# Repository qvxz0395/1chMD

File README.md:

# MD
## 要求仕様
  - 1ch
  - RZ735VA500W駆動可能
  - 出来ればPWM周波数50kHz(maxon motor controllerと同じ値)
  - 正転逆転
  - 電流制御
  - 速度制御
  - AMT102対応
  - CAN通信
  - 超小型,ターミナル方式

## 部品
  - メインマイコン
    - [STM32F042K6T6](http://akizukidenshi.com/catalog/g/gI-10789/)
    - [データシート](https://www.st.com/resource/en/datasheet/stm32f042c4.pdf) 
    - [リファレンスマニュアル](https://www.aps-web.jp/magazine/st/data/STM32F0x1_2_8RM_RM0091_JPN_rev1.pdf)

      - 250YEN
      - CAN 
      - 電流検出ADC12Bit
      - 書き込みデバッグ JTAG
      - ロータリーエンコーダ入力
      - とりあえず生やしとくピン
        - 4PDIPスイッチ
        - SPI1ch
        - USART1ch

  - CANトランシーバ
    - [ATA6561-GAQW-N](https://www.digikey.jp/product-detail/ja/microchip-technology/ATA6561-GAQW-N/ATA6561-GAQW-NCT-ND/9453180)
      - 63YEN
      - SOIC08
      - 電源 5V
      - 

  - 電流センサ
    - [ACS781KLRTR-150U-T](https://www.digikey.jp/product-detail/ja/allegro-microsystems-llc/ACS781KLRTR-150U-T/620-1851-1-ND/6677748)
      - 605YEN
      - ホール効果での電流検出
      - 検出可能電流 0~100[A] 過渡的に150[A], 17.6mV/A
      - 絶対最大定格 285[A],25℃
      - 

  - FET
    - [FDBL86561-F085](https://www.digikey.jp/product-detail/ja/on-semiconductor/FDBL86561-F085/FDBL86561-F085CT-ND/5209201)
      - 450 YEN @1
      - ドレインソース間電圧$V_{dss}$= 60[V]
      - ドレインソース間連続電流( $V_{gs}$ = 10[V], $T_c$ = 25[℃]) $I_D$= 300[A]
      - $I_d,V_{gs}$印加時の$R_{ds} On$= 1.1[mΩ] (max) @ 80[A] , 10[V]
      - $V_{gs}$印加時のゲート電荷 $Q_g$= 220[nC] (max) @10[V]
      - パッケージ　8-PowerSFN
    - 似た特性,同じパッケージのFET
      - [IPT007N06NATMA1](https://www.digikey.jp/product-detail/ja/infineon-technologies/IPT007N06NATMA1/IPT007N06NATMA1CT-ND/4571878)
      - [FDBL0110N60](https://www.digikey.jp/product-detail/ja/on-semiconductor/FDBL0110N60/FDBL0110N60CT-ND/5216101)

  - ゲートドライバ
    - [A3921KLPTR-T](http://akizukidenshi.com/catalog/g/gI-12293/)
      - 350YEN
      - フルブリッジMOSFETドライバ

  - 3.3Vレギュレータ
    - [NJM2845DL1-33](http://akizukidenshi.com/catalog/g/gI-11299/)
      - 50YEN
      - 最大入力電圧 14[V]
      - 出力電流　0.8[A]

  - 5Vレギュレータ
    - [NJM7805SDL1](http://akizukidenshi.com/catalog/g/gI-11237/)
      - 30YEN
      - 最大入力電圧 35[V]
      - 出力電流 1.5[A]

  - デジタルアイソレータ
    - [ADuM7440](https://www.digikey.jp/product-detail/ja/analog-devices-inc/ADUM7440ARQZ-RL7/ADUM7440ARQZ-RL7CT-ND/3897187)
      - 605YEN
      - 電源電圧 3-5.5[V]
      - 4Ch
      - データレート 1[Mbps]

  - モード変更用DIPSW
    - [EHS104LD](http://akizukidenshi.com/catalog/g/gP-05064/)

  - ショットキーバリアダイオード
    - 
## 計算(パワー回路設計)
  - [TeXコマンドをmarkdownでつかう方法](https://qiita.com/kgoto/items/2452b6dbaed5b3f7df78)

### ゲート抵抗
  - [参考](https://detail-infomation.com/gate-driver-gate-resistance-design/)

  FDBL86561-F085 のデータシートの表 Electrical Characteristics より
  
  Total Gate Charge $Q_g$ = 170[nC] (typ.) @ 10V 

  これより，

  ゲート駆動電圧 = 10[V]

  A3921KLPTR-T のデータシート表 ELECTRICAL CHARACTERISTICS Pulldown On Resistance 内の $I_{GHx} , I_{GLx}$より
  
  ゲート電流$I_G$= 150[mA]
  
  ゲート駆動回路の出力電圧$V_{OUT}= V_{REG} = 12.8[V]$より，(A3921の電気特性表より)

  ゲート抵抗$R_G$は

  $$ R_G = \dfrac{V_{out}}{I_G} = \dfrac{12.8[V]}{0.15[A]} = 85[Ω] $$

  ところで，
  電流iを時間tで積分したものが電荷$Q$なので，

  $$Q = \int idt$$

  ゲート電流$i_G$が時間$t_{ON}$流れることで，ゲートに蓄えられた電荷量が$Q_g$になる．

  $$Q_g = \int_0^{t_{ON}} I_G dt = I_G [t]_0^{t_{ON}} = I_G t_{ON}$$

  上記の関係より，

  $$ t_{ON} = \dfrac{Q_g}{t_{ON}} = \dfrac{170[nC]}{0.15[A]} = 1134[ns] $$

### デッドタイム

### チャージポンプコンデンサ

### ブートストラップコンデンサ

### 正逆転確認LEDの電流制限抵抗

### FFの電流制限抵抗

### 5V電源の電流制限抵抗

### 周波数

### 発熱

FETの発熱を考える．([参考](https://lab.fujiele.co.jp/articles/3129/))
他で発熱を考える必要があるのはゲートドライバICだけど，今回は無視．

損失は主に2種類ある．「オン抵抗と電流」によるものと「スイッチング損失」によるもの．

#### オン抵抗と電流

  $P = I^2R$

#### スイッチング損失

  FETはスイッチング時に損失が発生する．損失の式は．

  $ああああああ$

## マイコン関連

### ロータリーエンコーダ
  - [参考(STM32＋HALでエンコーダ―モード)](https://garberas.com/archives/244)

  - [参考(3.3V-5Vレベル変換)](http://kosakai.world.coocan.jp/change_3_3V_5V.html)

#### 回路
  よく使うインクリメンタルエンコーダ[AMT102](https://www.cui.com/product/resource/amt10.pdf)は電源$VDD=5$[V]駆動で,
  パルス信号出力も5[V]である．
  
  しかし，マイコンは3.3V駆動である．

  そのため，マイコンのピンの耐圧が5V以下だった場合，出力信号を[分圧](http://www.kairo-nyumon.com/resistor_divider.html)して電圧を落とさないといけない．

  マイコンの耐圧を確認する．今回の設計ではPA6とPB5,PB6が，エンコーダに接続されている．  
  データシートのP33からあるTable.13 pin definitionによると，それぞれのピンのI/O structureは順にTTa,FT,FTfである．  
  Table.12によると，TTaの耐圧が3.3V, FT,FTfの耐圧が5Vとなっている．また，Table18の絶対最大定格にはFT,FTfも内部プルアップ，プルダウンをすると**耐圧が下がる**と注3に書いてあるので，気を付ける．
  
  PA6だけは分圧必須である．（もう発注しちゃった，，，2019/08/21回路図及び配線図を修正）

#### プログラム

リファレンスマニュアルp341～にエンコーダインターフェースモードについての説明がある．

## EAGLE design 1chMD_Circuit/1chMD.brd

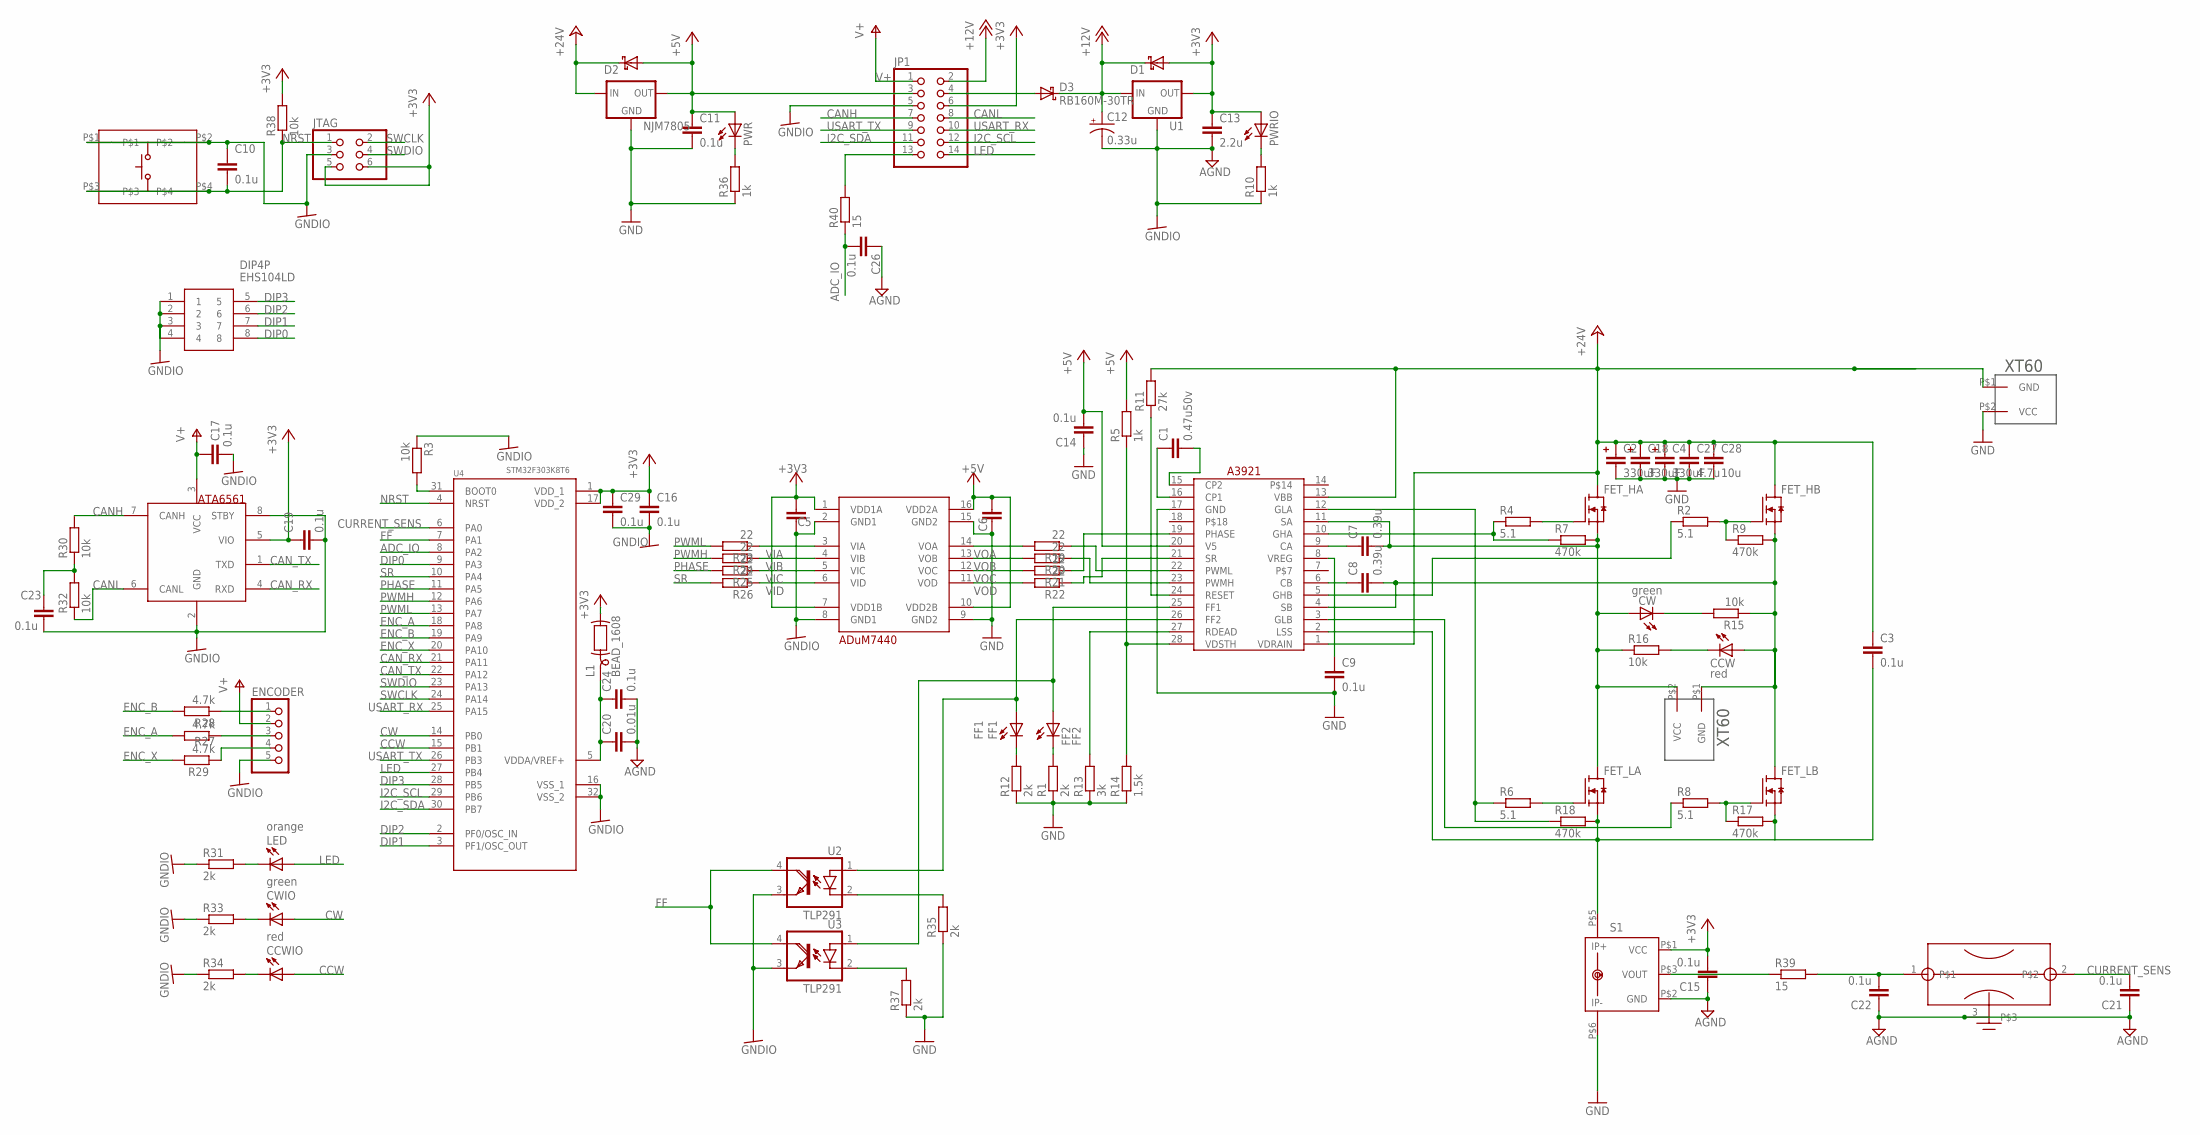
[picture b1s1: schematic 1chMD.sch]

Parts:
A3921: A3921; TSSOP28
ADUM7440: ADUM7440; QSOP16
ATA6561: ATA6561; SO_8
C1: 0.47u50v; 1608
C2, C4, C18: 330uF; PANASONIC_G
C3, C9, C10, C11, C14, C15, C16, C17, C19, C21, C22, C23, C24, C26, C29: 0.1u; 1608
C5, C6: C_1608; 1608
C7, C8: 0.39u; 1608
C12: 0.33u; PANASONIC_C
C13: 2.2u; 1608
C20: 0.01u; 1608
C25: NFM18PS474R0J3D; 1608_EMIFIL
C27: 4.7u; C0805K
C28: 10u; C1210K
CCW: red; 1608_POLE
CCWIO: red; 1608_POLE
CW: green; 1608_POLE
CWIO: green; 1608_POLE
D1, D2: RB751S-40; 1608_POLE
D3: RB160M-30TR; SODFL260X160X90L70X90N
DIP4P: EHS104LD
ENCODER: PINHD-1X5/90; 1X05/90
FET_HA: FDBL86561_F085; PG-HSOF-8-1
FET_HB: FDBL86561_F085; PG-HSOF-8-1
FET_LA: FDBL86561_F085; PG-HSOF-8-1
FET_LB: FDBL86561_F085; PG-HSOF-8-1
FF1: FF1; 1608_POLE
FF2: FF2; 1608_POLE
JP1: PINHD-2X7/90; 2X07/90
JTAG: PINHD-2X3/90; 2X03/90
L1: BEAD_1608; 1608
LED: orange; 1608_POLE
NJM7805: NJM7805SDL1; TO252
P2, P4: XT60-SMD; XT60-ANGLED
PWR: LED_1608; 1608_POLE
PWRIO: LED_1608; 1608_POLE
R1, R12, R31, R33, R34, R35, R37: 2k; 1608
R2, R4, R6, R8: 5.1; 1608
R3, R15, R16, R30, R32, R38: 10k; 1608
R5, R10, R36: 1k; 1608
R7, R9, R17, R18: 470k; 1608
R11: 27k; 1608
R13: 3k; 1608
R14: 1.5k; 1608
R19, R20, R21, R22, R23, R24, R25, R26: 22; 1608
R27, R28, R29: 4.7k; 1608
R39, R40: 15; 1608
S1: ACS781KLRTR-150U-T; 7-PIN_PSOF
SW1: SKRPACE010
U1: NJM2845; TO252
U2, U3: TLP291; SOIC127P265X700X230-4N
U4: STM32F303K8T6; QFP80P900X900X160-32N

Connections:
+3V3: ADUM7440.1 (VDD1A), ADUM7440.7 (VDD1B), ATA6561.5 (VIO), C5.1, C13.1, C15.2, C16.1, C19.1, C29.1, D1.2 (A), JP1.6, JTAG.5, JTAG.6, L1.2, PWRIO.2 (A), R38.2, S1.P$1 (VCC), U1.2 (OUT), U4.1 (VDD_1), U4.17 (VDD_2)
+5V: A3921.20 (V5), ADUM7440.10 (VDD2B), ADUM7440.16 (VDD2A), C6.2, C11.1, C14.2, D2.2 (A), JP1.3, NJM7805.2 (OUT), PWR.2 (A), R5.2
+12V: C12.+, D1.1 (C), D3.2 (C), JP1.2, U1.1 (IN)
+24V: A3921.1 (VDRAIN), A3921.13 (VBB), C2.+ (1), C3.1, C4.+ (1), C18.+ (1), C27.1, C28.1, D2.1 (C), FET_HA.9 (D), FET_HB.9 (D), NJM7805.1 (IN), P2.P$1 (GND), R11.2
ADC_IO: C26.2, R40.1, U4.8 (PA2)
AGND: C12.-, C13.2, C15.1, C20.2, C21.1, C22.1, C24.2, C25.3, C26.1, R10.1, S1.P$2 (GND), U1.3 (GND)
CANH: ATA6561.7 (CANH), JP1.7, R30.2
CANL: ATA6561.6 (CANL), JP1.8, R32.1
CAN_RX: ATA6561.4 (RXD), U4.21 (PA11)
CAN_TX: ATA6561.1 (TXD), U4.22 (PA12)
CCW: CCWIO.2 (A), U4.15 (PB1)
CURRENT_SENS: C21.2, C25.2, U4.6 (PA0)
CW: CWIO.2 (A), U4.14 (PB0)
DIP0: DIP4P.8, U4.9 (PA3)
DIP1: DIP4P.7, U4.3 (PF1/OSC_OUT)
DIP2: DIP4P.6, U4.2 (PF0/OSC_IN)
DIP3: DIP4P.5, U4.28 (PB5)
ENC_A: R27.2, U4.18 (PA8)
ENC_B: R28.2, U4.19 (PA9)
ENC_X: R29.2, U4.20 (PA10)
FF: U2.4 (COL), U3.4 (COL), U4.7 (PA1)
GND: A3921.17 (GND), ADUM7440.9 (GND2), ADUM7440.15 (GND2), C2.- (2), C4.- (2), C6.1, C9.2, C11.2, C14.1, C18.- (2), C27.2, C28.2, NJM7805.3 (GND), P2.P$2 (VCC), R1.1, R12.1, R13.1, R14.1, R35.1, R36.1, R37.1, S1.P$6 (IP-)
GNDIO: ADUM7440.2 (GND1), ADUM7440.8 (GND1), ATA6561.2 (GND), ATA6561.8 (STBY), C5.2, C10.1, C16.2, C17.2, C19.2, C23.2, C29.2, DIP4P.1, DIP4P.2, DIP4P.3, DIP4P.4, ENCODER.5, JP1.5, JTAG.3, R3.1, R31.1, R33.1, R34.1, SW1.P$1, SW1.P$2, U2.3 (EMI), U3.3 (EMI), U4.16 (VSS_1), U4.32 (VSS_2)
I2C_SCL: JP1.12, U4.29 (PB6)
I2C_SDA: JP1.11, U4.30 (PB7)
LED: JP1.14, LED.2 (A), U4.27 (PB4)
unnamed: FET_HB.1 (G), R2.2, R9.1
unnamed: A3921.24 (RESET), R11.1
unnamed: FET_LB.1 (G), R8.2, R17.1
unnamed: A3921.8 (VREG), C9.1
unnamed: FET_LA.1 (G), R6.2
unnamed: FET_HA.1 (G), R4.2
unnamed: A3921.25 (FF1), FF2.2 (A), U3.1 (A)
unnamed: PWRIO.1 (C), R10.2
unnamed: PWR.1 (C), R36.2
unnamed: A3921.9 (CA), C7.1
unnamed: A3921.10 (GHA), R4.1, R7.1
unnamed: A3921.6 (CB), C8.1
unnamed: A3921.5 (GHB), R2.1
unnamed: A3921.12 (GLA), R6.1, R18.1
unnamed: A3921.3 (GLB), R8.1
unnamed: A3921.26 (FF2), FF1.2 (A), U2.1 (A)
unnamed: A3921.4 (SB), C8.2, CCW.2 (A), FET_HB.2-8 (S), FET_LB.9 (D), P4.P$1 (GND), R9.2, R15.1
unnamed: FF2.1 (C), R1.2
unnamed: FF1.1 (C), R12.2
unnamed: A3921.16 (CP1), C1.1
unnamed: A3921.15 (CP2), C1.2
unnamed: A3921.27 (RDEAD), R13.2
unnamed: A3921.22 (PWML), R19.1
unnamed: A3921.23 (PWMH), R20.1
unnamed: A3921.19 (PHASE), R21.1
unnamed: A3921.2 (LSS), C3.2, FET_LA.2-8 (S), FET_LB.2-8 (S), R17.2, R18.2, S1.P$5 (IP+)
unnamed: A3921.28 (VDSTH), R5.1, R14.2
unnamed: A3921.21 (SR), R22.1
unnamed: CW.1 (C), R15.2
unnamed: CCW.1 (C), R16.2
unnamed: LED.1 (C), R31.2
unnamed: CWIO.1 (C), R33.2
unnamed: CCWIO.1 (C), R34.2
unnamed: ENCODER.3, R27.1
unnamed: R3.2, U4.31 (BOOT0)
unnamed: R39.1, S1.P$3 (VOUT)
unnamed: R35.2, U2.2 (C)
unnamed: ENCODER.4, R29.1
unnamed: ENCODER.1, R28.1
unnamed: R37.2, U3.2 (C)
unnamed: JP1.13, R40.2
unnamed: A3921.11 (SA), C7.2, CW.2 (A), FET_HA.2-8 (S), FET_LA.9 (D), P4.P$2 (VCC), R7.2, R16.1
unnamed: C23.1, R30.1, R32.2
unnamed: D3.1 (A), JP1.4
unnamed: C20.1, C24.1, L1.1, U4.5 (VDDA/VREF+)
NRST: C10.2, JTAG.1, R38.1, SW1.P$3, SW1.P$4, U4.4 (NRST)
PHASE: R25.2, U4.11 (PA5)
PWMH: R24.2, U4.12 (PA6)
PWML: R23.2, U4.13 (PA7)
SR: R26.2, U4.10 (PA4)
SWCLK: JTAG.2, U4.24 (PA14)
SWDIO: JTAG.4, U4.23 (PA13)
USART_RX: JP1.10, U4.25 (PA15)
USART_TX: JP1.9, U4.26 (PB3)
V+: ATA6561.3 (VCC), C17.1, ENCODER.2, JP1.1
VIA: ADUM7440.3 (VIA), R23.1
VIB: ADUM7440.4 (VIB), R24.1
VIC: ADUM7440.5 (VIC), R25.1
VID: ADUM7440.6 (VID), R26.1
VOA: ADUM7440.14 (VOA), R19.2
VOB: ADUM7440.13 (VOB), R20.2
VOC: ADUM7440.12 (VOC), R21.2
VOD: ADUM7440.11 (VOD), R22.2
VOUT: C22.2, C25.1, R39.2

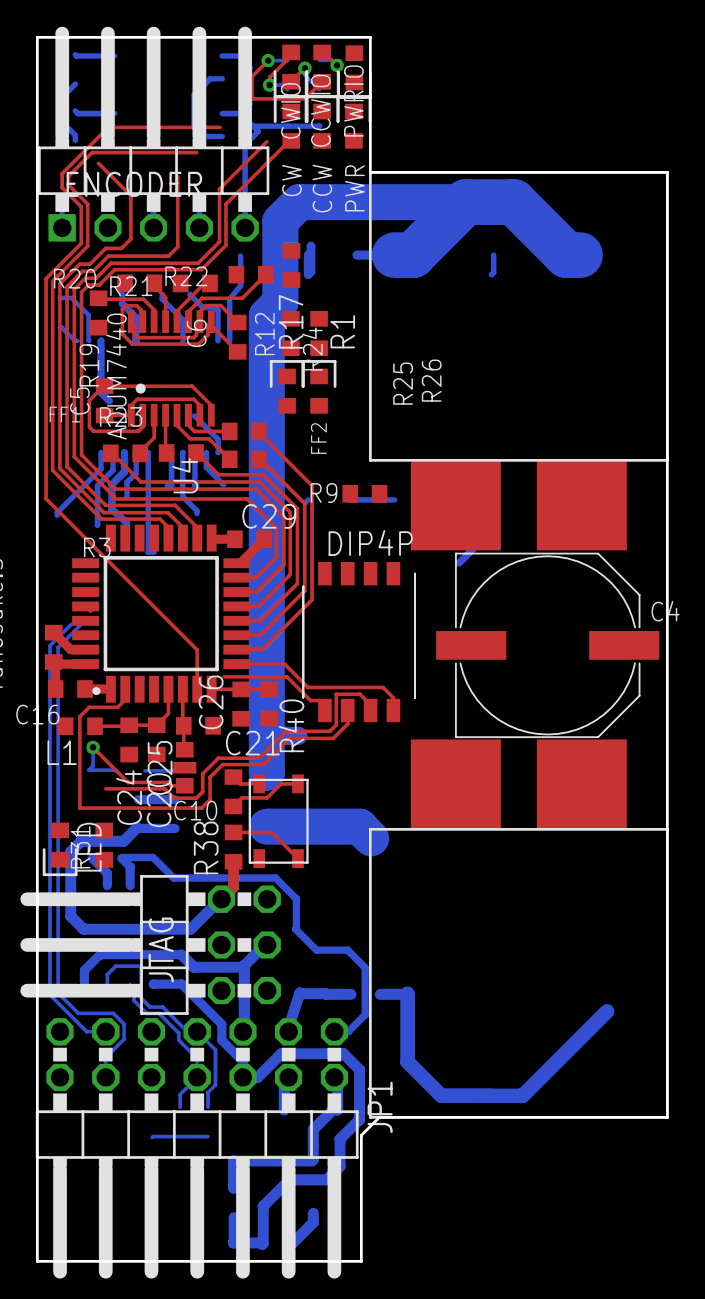
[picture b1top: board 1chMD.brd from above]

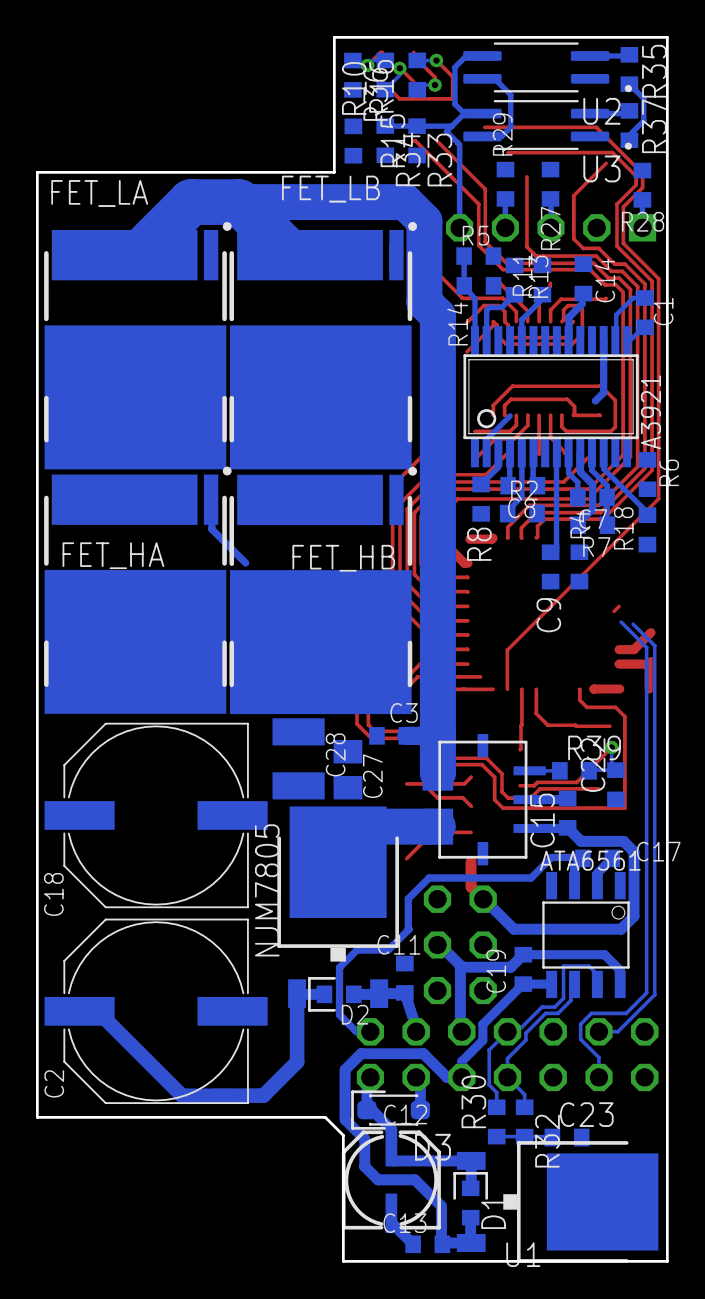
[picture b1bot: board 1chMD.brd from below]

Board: 2 copper layers, 35.0 x 68.0 mm, 102 parts (56 on the bottom side), 90 nets.

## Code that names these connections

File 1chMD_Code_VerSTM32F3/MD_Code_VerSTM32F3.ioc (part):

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Mcu.Name=STM32F303K(6-8)Tx
Mcu.Package=LQFP32
Mcu.UserName=STM32F303K8Tx
PA0.GPIOParameters=GPIO_Label
PA0.GPIO_Label=CURRENT_SENS
PA0.Mode=IN1-Single-Ended
PA0.Signal=ADC1_IN1
PA1.GPIOParameters=GPIO_PuPd,GPIO_Label
PA1.GPIO_Label=FF1
PA1.GPIO_PuPd=GPIO_PULLUP
PA1.Signal=GPIO_Input
PA10.GPIOParameters=GPIO_Label
PA10.GPIO_Label=ENC_X
PA10.Signal=GPIO_Input
PA11.Mode=Master
PA11.Signal=CAN_RX
PA12.Mode=Master
PA12.Signal=CAN_TX
PA13.Mode=Serial_Wire
PA13.Signal=SYS_JTMS-SWDIO
PA14.Mode=Serial_Wire
PA14.Signal=SYS_JTCK-SWCLK
PA15.Mode=Asynchronous
PA15.Signal=USART2_RX
PA2.GPIOParameters=GPIO_Label
PA2.GPIO_Label=ADC_IO
PA2.Mode=IN3-Single-Ended
PA2.Signal=ADC1_IN3
PA3.GPIOParameters=GPIO_PuPd,GPIO_Label
PA3.GPIO_Label=DIP0
PA3.GPIO_PuPd=GPIO_PULLUP
PA3.Signal=GPIO_Input
PA4.GPIOParameters=GPIO_Label
PA4.GPIO_Label=SR
PA4.Signal=GPIO_Output
PA5.GPIOParameters=GPIO_Label
PA5.GPIO_Label=PHASE
PA5.Signal=GPIO_Output
PA6.GPIOParameters=GPIO_Label
PA6.GPIO_Label=PWMH
PA6.Signal=S_TIM3_CH1
PA7.GPIOParameters=GPIO_Label
PA7.GPIO_Label=PWML
PA7.Signal=S_TIM3_CH2
PA8.GPIOParameters=GPIO_Label
PA8.GPIO_Label=ENC_A
PA8.Signal=S_TIM1_CH1
PA9.GPIOParameters=GPIO_Label
PA9.GPIO_Label=ENC_B
PA9.Signal=S_TIM1_CH2
PB0.GPIOParameters=GPIO_Label
PB0.GPIO_Label=CW
PB0.Signal=S_TIM3_CH3
PB1.GPIOParameters=GPIO_Label
PB1.GPIO_Label=CCW
PB1.Signal=S_TIM3_CH4
PB3.Mode=Asynchronous
PB3.Signal=USART2_TX
PB4.GPIOParameters=GPIO_Label
PB4.GPIO_Label=LED
PB4.Signal=GPIO_Output
PB5.GPIOParameters=GPIO_PuPd,GPIO_Label
PB5.GPIO_Label=DIP3
PB5.GPIO_PuPd=GPIO_PULLUP
PB5.Signal=GPIO_Input
PB6.Mode=I2C
PB6.Signal=I2C1_SCL
PB7.Mode=I2C
PB7.Signal=I2C1_SDA
PF0\ /\ OSC_IN.GPIOParameters=GPIO_PuPd,GPIO_Label
PF0\ /\ OSC_IN.GPIO_Label=DIP2
PF0\ /\ OSC_IN.GPIO_PuPd=GPIO_PULLUP
PF0\ /\ OSC_IN.Signal=GPIO_Input
PF1\ /\ OSC_OUT.GPIOParameters=GPIO_PuPd,GPIO_Label
PF1\ /\ OSC_OUT.GPIO_Label=DIP1
PF1\ /\ OSC_OUT.GPIO_PuPd=GPIO_PULLUP
PF1\ /\ OSC_OUT.Signal=GPIO_Input
RCC.HSEPLLFreq_Value=8000000
RCC.HSE_VALUE=8000000
RCC.SYSCLKFreq_VALUE=8000000
board=custom

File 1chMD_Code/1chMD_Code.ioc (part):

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Mcu.Name=STM32F042K(4-6)Tx
Mcu.Package=LQFP32
Mcu.UserName=STM32F042K6Tx
PA0.GPIOParameters=GPIO_ModeDefaultPP,GPIO_Speed,GPIO_PuPd,GPIO_Label
PA0.GPIO_Label=PWMH
PA0.GPIO_ModeDefaultPP=GPIO_MODE_AF_PP
PA0.GPIO_PuPd=GPIO_NOPULL
PA0.GPIO_Speed=GPIO_SPEED_FREQ_LOW
PA0.Signal=S_TIM2_CH1_ETR
PA1.GPIOParameters=GPIO_Label
PA1.GPIO_Label=PWML
PA1.Signal=S_TIM2_CH2
PA10.GPIOParameters=GPIO_ModeDefaultPP,GPIO_Speed,GPIO_FMA10,GPIO_PuPd,GPIO_Label
PA10.GPIO_FMA10=__NULL
PA10.GPIO_Label=USART_RX
PA10.GPIO_ModeDefaultPP=GPIO_MODE_AF_PP
PA10.GPIO_PuPd=GPIO_NOPULL
PA10.GPIO_Speed=GPIO_SPEED_FREQ_HIGH
PA10.Mode=Asynchronous
PA10.Signal=USART1_RX
PA11.Mode=Master
PA11.Signal=CAN_RX
PA12.Mode=Master
PA12.Signal=CAN_TX
PA13.GPIOParameters=GPIO_Label
PA13.GPIO_Label=SWDIO
PA13.Mode=Serial_Wire
PA13.Signal=SYS_SWDIO
PA14.GPIOParameters=GPIO_Label
PA14.GPIO_Label=SWDIO
PA14.Mode=Serial_Wire
PA14.Signal=SYS_SWCLK
PA2.GPIOParameters=GPIO_Speed,PinState,GPIO_PuPd,GPIO_Label,GPIO_ModeDefaultOutputPP
PA2.GPIO_Label=SR
PA2.GPIO_ModeDefaultOutputPP=GPIO_MODE_OUTPUT_PP
PA2.GPIO_PuPd=GPIO_NOPULL
PA2.GPIO_Speed=GPIO_SPEED_FREQ_LOW
PA2.PinState=GPIO_PIN_RESET
PA2.Signal=GPIO_Output
PA3.GPIOParameters=GPIO_Label
PA3.GPIO_Label=PHASE
PA3.Signal=GPIO_Output
PA4.GPIOParameters=GPIO_Label
PA4.GPIO_Label=CAN_STBY
PA4.Signal=GPIO_Output
PA5.GPIOParameters=GPIO_Label
PA5.GPIO_Label=LED1
PA5.Signal=GPIO_Output
PA6.GPIOParameters=GPIO_ModeDefaultPP,GPIO_Speed,GPIO_PuPd,GPIO_Label
PA6.GPIO_Label=ENC_A
PA6.GPIO_ModeDefaultPP=GPIO_MODE_AF_PP
PA6.GPIO_PuPd=GPIO_NOPULL
PA6.GPIO_Speed=GPIO_SPEED_FREQ_LOW
PA6.Signal=S_TIM3_CH1
PA7.GPIOParameters=GPIO_Speed,GPIO_PuPd,GPIO_Mode
PA7.GPIO_Mode=GPIO_MODE_AF_PP
PA7.GPIO_PuPd=GPIO_NOPULL
PA7.GPIO_Speed=GPIO_SPEED_FREQ_HIGH
PA7.Signal=SPI1_MOSI
PA8.GPIOParameters=GPIO_Label
PA8.GPIO_Label=FF1
PA8.Signal=GPIO_Input
PA9.GPIOParameters=GPIO_ModeDefaultPP,GPIO_Speed,GPIO_FMA9,GPIO_PuPd,GPIO_Label
PA9.GPIO_FMA9=__NULL
PA9.GPIO_Label=USART_TX
PA9.GPIO_ModeDefaultPP=GPIO_MODE_AF_PP
PA9.GPIO_PuPd=GPIO_NOPULL
PA9.GPIO_Speed=GPIO_SPEED_FREQ_HIGH
PA9.Mode=Asynchronous
PA9.Signal=USART1_TX
PB0.GPIOParameters=GPIO_Label
PB0.GPIO_Label=FF2
PB0.Signal=GPIO_Input
PB1.GPIOParameters=GPIO_PuPd,GPIO_Label,GPIO_Mode
PB1.GPIO_Label=VOUT
PB1.GPIO_Mode=GPIO_MODE_ANALOG
PB1.GPIO_PuPd=GPIO_NOPULL
PB1.Mode=IN9
PB1.Signal=ADC_IN9
PB5.GPIOParameters=GPIO_ModeDefaultPP,GPIO_Speed,GPIO_PuPd,GPIO_Label
PB5.GPIO_Label=ENC_B
PB5.GPIO_ModeDefaultPP=GPIO_MODE_AF_PP
PB5.GPIO_PuPd=GPIO_NOPULL
PB5.GPIO_Speed=GPIO_SPEED_FREQ_LOW
PB5.Signal=S_TIM3_CH2
PB6.GPIOParameters=GPIO_PuPd,GPIO_Label,GPIO_ModeDefaultEXTI
PB6.GPIO_Label=ENC_X
PB6.GPIO_ModeDefaultEXTI=GPIO_MODE_IT_RISING
PB6.GPIO_PuPd=GPIO_NOPULL
PB6.Signal=GPXTI6
PB7.GPIOParameters=GPIO_PuPd,GPIO_Label,GPIO_Mode
PB7.GPIO_Label=DIP3
PB7.GPIO_Mode=GPIO_MODE_INPUT
PB7.GPIO_PuPd=GPIO_PULLUP
PB7.Signal=GPIO_Input
PB8.Signal=S_TIM16_CH1
RCC.SYSCLKFreq_VALUE=48000000
RCC.SYSCLKSource=RCC_SYSCLKSOURCE_HSI48
board=custom

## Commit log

2019-10-01 CubeIDEでプロジェクト立ち上げた．何もしないプログラムの書き込み完了
2019-10-01 参考資料とデータシートの追跡をしない
2019-10-01 .iocで使う機能を生成．コンパイル通った
2019-10-01 モータを低速で正逆転できることを確認．ただ，今はFETのHigh側のみでPWMを出しているので，ブートストラップの充電時間によるDuty上限制限が存在する．一定以上のDutyになったらLow側のFETでPWMを行うように変更することが必要．電流センサ周りも記入はしているが動作未確認．後移動平均フィルタよりもLPFのほうが高速に計算できるかも．
2019-10-01 STM Studioでのデバッグを行った．Dutyが絶対値表記になっているのを直したい．
2019-10-01 回路図整理途中
2019-10-02 775の摺動部に油差したらDuty1．5でも回ったw油刺さない状態だとDuty2.5が限界だったけど
2019-10-02 STMのデータシート追加
2019-10-02 Dutyの値がおかしいの解決．
2019-10-02 MDのプログラム， 0～高PWMまでをHi側FETで，高PWM～100％までをLo側FETで出力するように変更． モータ回してみたら爆速で回ってしまったので，なんかエラーがあるけど眠いのでお預け
2019-10-02 CMSIS_DSPライブラリを導入できた．コンパイルできない原因はメモリ不足．SPIなどのとりあえず使わない機能を消してダイエットしたら書き込めた．
2019-10-02 LPFのADC読み取りにしてみた．なんか知らんが起動から3秒くらいしないとADCの値が振れない
2019-10-05 電流制御できた．
2019-10-11 SPI,I2Cをひとまず削除。メモリ削減のため。CANの同格途中。まだ動いてない。エラーはいてる。
2019-10-12 CANの送信は出来てる？(エラーは出てない) 受信はエラー．
2019-10-15 CANの送信は出来てるっぽい．送信できなかった原因はCANのトランシーバのTxRxを逆に接続してたから．ちゃんと内部回路図見て配線しないとだめだなｗ 受信は確認できてない．(サーキュラーモードで確認しようとしたけど，メモリ不足で書き込みできなかった．)
2019-10-15 V2の回路図書き途中．後EMIふぃるとFFのフォトカプラ，10う，1うのCをつければほぼ終わり
2019-10-15 STM32F303版のCubeIDEプロジェクト．IOコンフィグは大方設定終わってる．
2019-10-16 回路図は完成．1日放置． 実体配線は30％くらい終わった．
2019-10-18 回路図でコンデンサの配置をもう少し実体配線に沿った形に変更．配線10％進んだ
2019-10-22 1％くらい進んだ
